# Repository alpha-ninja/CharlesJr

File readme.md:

# Charles Jr.

A tiny PCB (0.25x0.25 inches), which charlieplexes (hence the name) 6 LEDs on 3 pins.

It was created because that size happens to be OSHPark's lower size limit—it costs 30¢ for 3 (without components)

It requires 3 resistors and 6 LEDs, both in 0603 format. It also uses a 3-pin header.

To calculate the value of the resistors, use (Vcc - Vf) / (If * 2)

So, for example, a LED that requires 20mA (0.02A) and has a forward voltage of 3v using a power supply with 5v needs:

    (5v - 3v) / (0.02A * 2)
    = 50Ω

The *2 in there is not usually used when calculating resistor values for LEDs. However, it is used here because charlieplexing requires 2 resistors—in series—for LEDs when it's wired the way it is here.  
Thus, for the LED and power supply in the example above, you would usually use a 100Ω resistor while this circuit would use 50Ω resistors.

Enjoy!

## LED groups, x/y values to control them:

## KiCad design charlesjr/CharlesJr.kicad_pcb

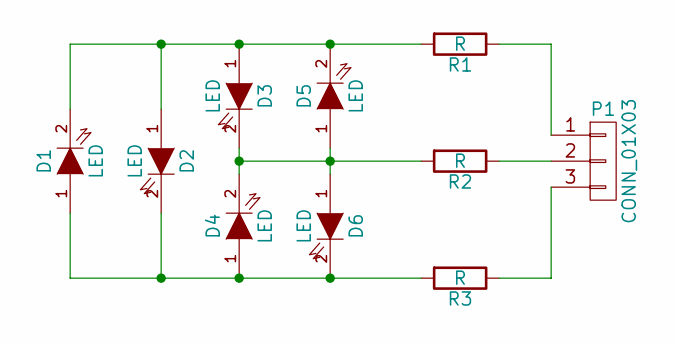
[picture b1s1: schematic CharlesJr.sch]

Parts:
D1, D2, D3, D4, D5, D6: LED; LED-0603
P1: CONN_01X03; Pin_Header_Angled_1x03
R1, R2, R3: R; R_0603

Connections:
unnamed: D1.1 (A), D2.2 (K), D4.1 (A), D6.2 (K), R3.2
unnamed: D1.2 (K), D2.1 (A), D3.1 (A), D5.2 (K), R1.2
unnamed: D3.2 (K), D4.2 (K), D5.1 (A), D6.1 (A), R2.2
unnamed: P1.1, R1.1
unnamed: P1.2, R2.1
unnamed: P1.3, R3.1

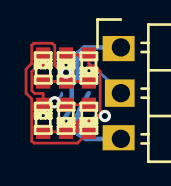
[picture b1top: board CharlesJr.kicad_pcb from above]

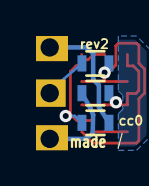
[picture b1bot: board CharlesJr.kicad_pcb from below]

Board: 2 copper layers, 10 parts (3 on the bottom side), 6 nets.

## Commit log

2015-05-15 Initial commit
    Add readme, gitignore, kicad files, gerbers, gerber zip
2015-05-15 Fix price
2015-05-15 Add more information about resistors in charlieplexed circuits
2015-05-30 Upload rev2.
    Improved silkscreen, higher track width for header to resistor
    connections, add "rev2" text.
2015-05-30 Add arduino library
2015-05-30 Wrap license.txt
2015-05-31 Add image
2015-05-31 Add ability to swap LED codes within a group; fix keywords

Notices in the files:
charlesjr/CharlesJr.kicad_pcb:
cc0
